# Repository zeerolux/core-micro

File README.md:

# Zeerolux Core-Micro

A lighting controller, control surface with 5 faders and 2 encoders, a USB DMX interface, an ARTNET node, and a standalone DMX generator. The Core-Micro system consists or 4 modules; the logic processor, the control surface, the DMX interface, and the redundant USB-C power supply. These modules are designed in a way that allows them to be iterated on separetly and allow for a limitless amount of configuration. How do you use Core-Micro? It depends on how YOU need to use it. Core-Micro can be used as a midi controller for On-PC lighting softwares, it can be used in a standalone mode where it acts like an all in one system for controlling stage lighting, and eventually it will be able to run in conjuction with other Zeerolux hardware and software as either the main controller or as a programming wing. It can also be used as an ARTNET node, this means that you can connect to it over the network and output DMX out its outputs.

### Defintions:
- DMX: Digital Multiplex is an RS485 based communication standard for controlling stage lights and equipment.
- ARTNET: DMX over IP
- On-PC: A standard term used by lighting consoles to describe control systems that require a laptop or PC to operate as opposed to all processing running on console.

### Why?
I decided to take on this project after I realised how incredibly expensive lighting consoles are. Out of curiosity, I wanted to see whether I could build my own console and what price it would turn out at. Another inspiration was my experience with the Avolites Quartz which to say the least was... frustrating, so naturally, I was fresh with ideas on what not to do.

## The Hardware
Core-Micro has four PCBs; one for each module. 

### Logic PCB:

The Logic PCB does a few main things:
- Connects to PC over USB
- Processes DMX signals and distrobutes them to DMX PCB(s)
- Runs ARTNET
- Interfaces with Surface PCB
All the main processing is powered by an RP2040 and the ethernet controller is a W5500.

### Control Surface PCB

This PCB's purpose is as follows:
- To have enough buttons to comfortably program lights
- To have enough faders for basic theatre applications
- To interface with the Logic board and passthrough control to PC applications or standalone mode.
Like the Logic PCB, the Control Surface is powered by an RP2040 and sends commands to other components via UART.

### Power PCB

Why do we need a separate PCB for power? Redundancy. In a live production environment, we cannot tolerate any power cuts or flaky USB connections. Therefore, I designed a board that has two inputs that can automatically be switched between if one cuts out. This allows for:
- Usage of independant power supplies for redundancy
- Automatic switch over to battery power during power cuts or brownouts
There is also a Superviser IC on this PCB in case I want to add that functionality in the future to other modules.

### DMX Interface PCB

This simple PCB converts the PIO DMX signal into RS485 signal that can be sent to DMX fixtures. This board also has both 3-pin and 5-pin XLR to ensure you can connect to any light.

## The Software

At this current moment, the software is a minimal version designed for testing DMX and ARTNET in a standalone mode. Here is the ideal list of software features I would like to implement:
- Standalone mode
- ARTNET node mode
- Midi Mode
- Custom serial driver for control via custom software

## BOM

## Bill of Materials (BOM)

| Item                          | Qty | Link / Supplier | List Price  | Actual  | Location    | Shipping  |
|--------------------------------|-----|-----------------|------------------|--------------|------------|----------------|
| Surface PCB                    | 5   | JLCPCB          | 17.90            | 190.94       | JLCPCB     | 33.14          |
| Surface PCB Assembly           | 2   | JLCPCB          | 39.89            | —            | aliexpress | —              |
| Logic PCB                      | 5   | JLCPCB          | 4.00             | —            | mouser     | 20.00          |
| Logic PCB Assembly             | 2   | JLCPCB          | 48.14            | —            | beekeeb    | 15.64          |
| DMX PCB                        | 5   | JLCPCB          | 4.00             | —            | —          | —              |
| DMX PCB Assembly               | 2   | JLCPCB          | 18.58            | —            | —          | —              |
| Power PCB                      | 5   | JLCPCB          | 2.00             | —            | —          | —              |
| Power PCB Assembly             | 2   | JLCPCB          | 43.29            | —            | —          | —              |
| Encoders                       | 3   | Mouser          | 5.07             | 5.07         | —          | —              |
| Faders                         | 5   | Mouser          | 9.60             | 9.60         | —          | —              |
| USB B Socket                   | 1   | Mouser          | 0.95             | 0.95         | —          | —              |
| Threaded Inserts M3            | 100 | AliExpress      | 5.00             | 5.00         | —          | —              |
| Threaded Inserts M2            | 100 | AliExpress      | 5.00             | 5.00         | —          | —              |
| Screws M3                      | 50  | AliExpress      | 3.00             | 3.00         | —          | —              |
| Screws M2                      | 50  | AliExpress      | 3.00             | 3.00         | —          | —              |
| Key Switches                   | 50  | Beekeeb         | 49.00            | 49.00        | —          | —              |
| Neutrik 3 Pin XLR              | 2   | Mouser          | 5.64             | 5.64         | —          | —              |
| Neutrik 5 Pin XLR              | 2   | Mouser          | 7.74             | 7.74         | —          | —              |
| Shipping (overall products)    | —   | —               | 68.78            | —            | —          | —              |
| **Total Cost**                 | —   | —               | **284.94**       | —            | —          | —              |

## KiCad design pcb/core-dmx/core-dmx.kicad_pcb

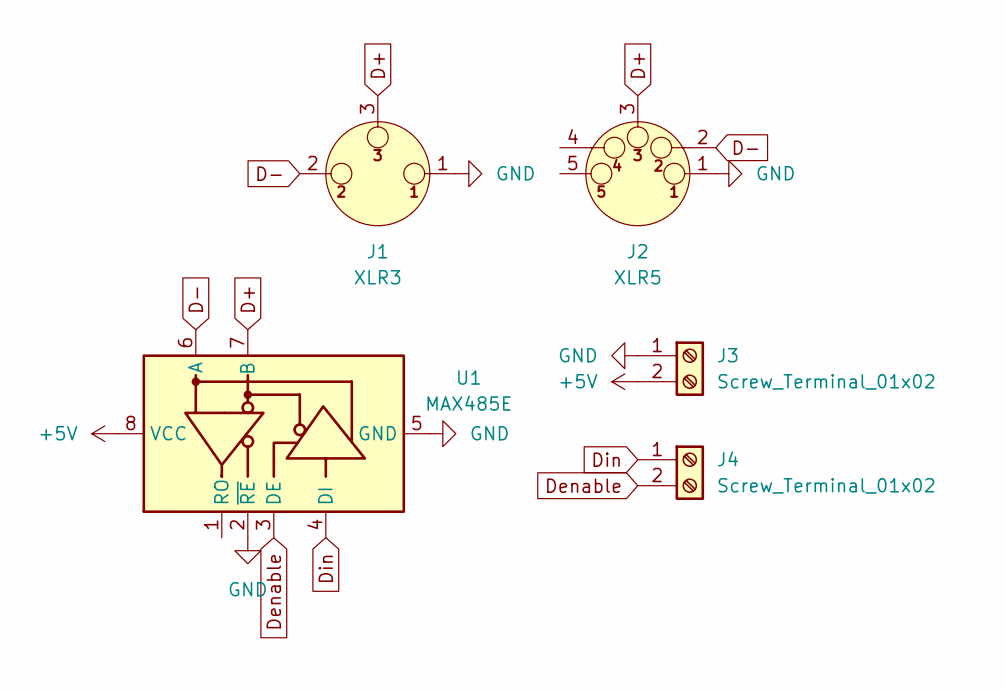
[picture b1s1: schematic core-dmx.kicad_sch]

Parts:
J1: XLR3; Jack_XLR_Neutrik_NC3FAH-0_Horizontal
J2: XLR5; Jack_XLR_Neutrik_NC5FAH-0_Horizontal
J3, J4: Screw_Terminal_01x02; TerminalBlock_Xinya_XY308-2.54-2P_1x02_P2.54mm_Horizontal
U1: MAX485E; SOIC-8_3.9x4.9mm_P1.27mm

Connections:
+5V: J3.2, U1.8 (VCC)
D+: J1.3, J2.3, U1.7 (B)
D-: J1.2, J2.2, U1.6 (A)
Denable: J4.2, U1.3 (DE)
Din: J4.1, U1.4 (DI)
GND: J1.1, J2.1, J3.1, U1.2 (~RE), U1.5 (GND)

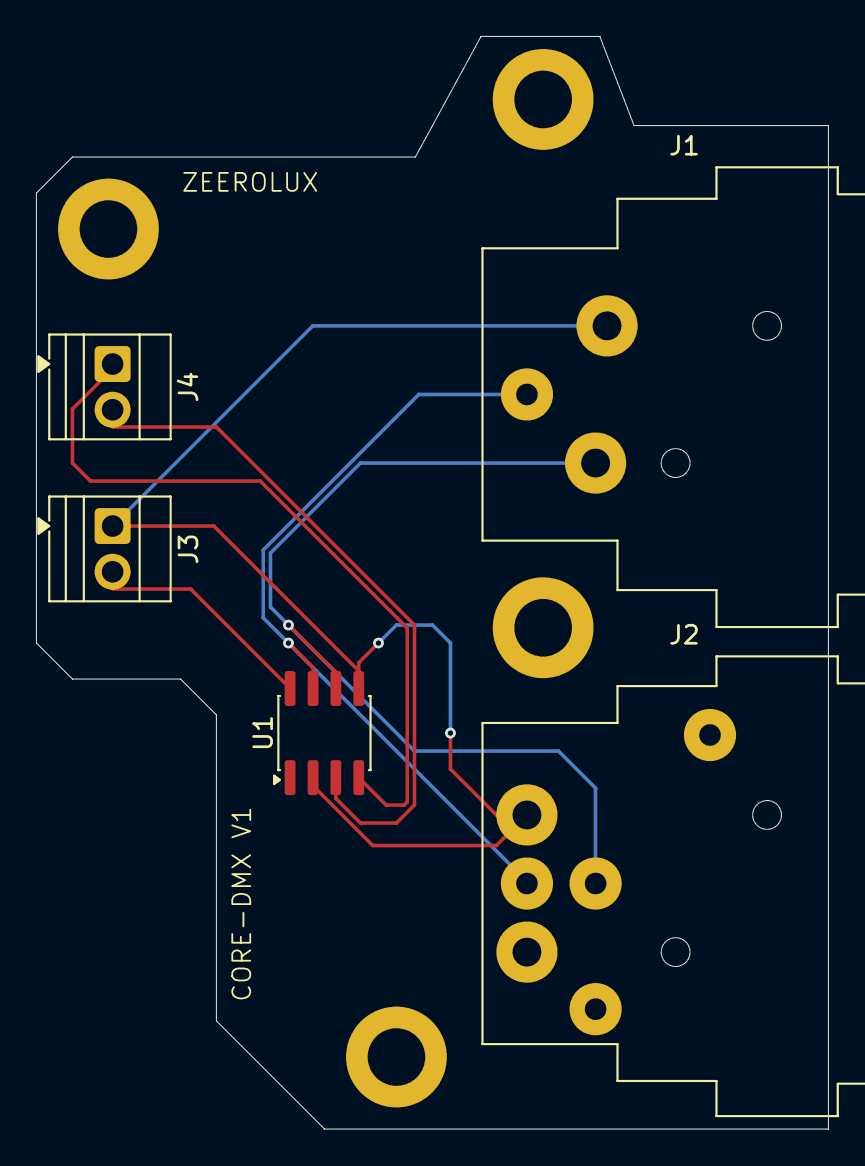
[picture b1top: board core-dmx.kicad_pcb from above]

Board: 2 copper layers, 44.0 x 60.7 mm, 5 parts (0 on the bottom side), 6 nets.

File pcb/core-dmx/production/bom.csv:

Designator,Footprint,Quantity,Value,LCSC Part #
"_3, _2, ",,3,,
"J3, J4",TerminalBlock_Xinya_XY308-2.54-2P_1x02_P2.54mm_Horizontal,2,Screw_Terminal_01x02,
U1,SOIC-8_3.9x4.9mm_P1.27mm,1,MAX485E,

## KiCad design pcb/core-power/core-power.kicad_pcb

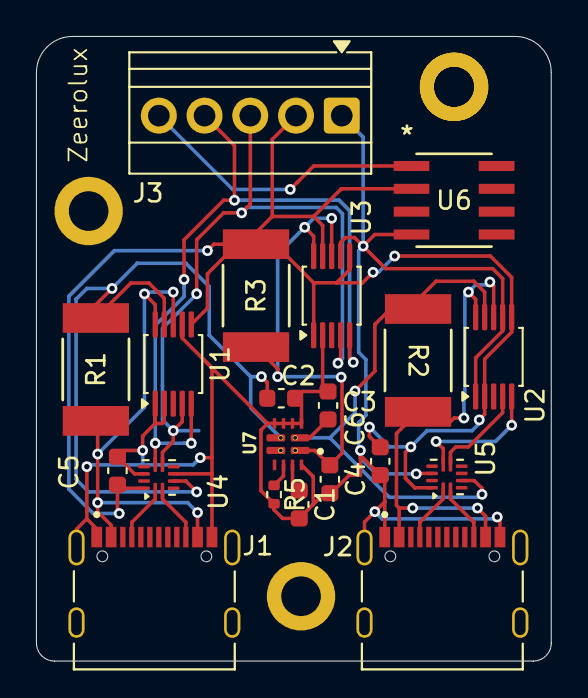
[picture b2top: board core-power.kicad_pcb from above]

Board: 2 copper layers, 28.6 x 34.7 mm, 20 parts (0 on the bottom side), 16 nets.

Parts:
C1: 22nF; C_0603_1608Metric
C2, C3: 10uF; C_0603_1608Metric
C4: 22uF; C_0603_1608Metric
C5, C6: 100nF; C_0603_1608Metric
J1, J2: USB_C_Receptacle_USB2.0_16P; HRO_TYPE-C-31-M-12
J3: Screw_Terminal_01x05; TerminalBlock_Xinya_XY308-2.54-5P_1x05_P2.54mm_Horizontal
R1, R2, R3: WSLP2512R0100FEA; RES_VISHAY_WSLP2512_C_VIS
R5: 5.5k; R_0402_1005Metric
U1, U2, U3: INA226; VSSOP-10_3x3mm_P0.5mm
U4, U5: TUSB320; Texas_X2QFN-12_1.6x1.6mm_P0.4mm
U6: MCP130T-315I/SN; SOIC8-N_MC_MCH
U7: TPS2121RUXR; IC_TPS2121RUXR

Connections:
CC1-1: J1.A5 (CC1), U4.1 (CC1)
CC1-2: J2.A5 (CC1), U5.1 (CC1)
CC2-1: J1.B5 (CC2), U4.2 (CC2)
CC2-2: J2.B5 (CC2), U5.2 (CC2)
GND: C1.2, C2.2, C3.2, C4.2, C5.2, C6.2, J1.GND, J1.S1 (SHIELD), J2.A1_B12, J2.B1_A12, J2.S1 (SHIELD), J3.1, R5.2, U1.1 (A1), U1.2 (A0), U1.7 (GND), U2.1 (A1), U2.7 (GND), U3.2 (A0), U3.7 (GND), U4.5 (ADDR), U4.10 (GND), U5.10 (GND), U6.4 (VSS), U7.3 (CP2), U7.4 (OV2), U7.5 (OV1), U7.6 (PR1), U7.12 (GND)
J1V+: J1.A4_B9, R1.1, U1.8 (Vbus), U1.10 (Vin+)
J1V-: C2.1, R1.2, U1.9 (Vin-), U4.4 (VBUS_DET), U7.7 (IN1), U7.7_1 (IN1__1)
J2V+: R2.2, U2.8 (Vbus), U2.10 (Vin+)
J2V-: C3.1, R2.1, U2.9 (Vin-), U5.4 (VBUS_DET), U7.2 (IN2), U7.2_1 (IN2__1)
MUXV+: C4.1, R3.1, U3.8 (Vbus), U3.10 (Vin+), U7.1 (OUT), U7.1_1 (OUT__1), U7.8 (OUT__2), U7.8_1 (OUT__3)
MUXV-: C5.1, C6.1, J3.2, R3.2, U1.6 (VS), U2.2 (A0), U2.6 (VS), U3.1 (A1), U3.6 (VS), U3.9 (Vin-), U4.12 (VDD), U5.5 (ADDR), U5.12 (VDD), U6.2 (VDD)
unnamed: R5.1, U7.10 (ILIM)
unnamed: C1.1, U7.11 (SS)
RESET: J3.5, U6.1 (*RST)
SCL: J3.4, U1.5 (SCL), U2.5 (SCL), U3.5 (SCL), U4.8 (SCL/OUT2), U5.8 (SCL/OUT2)
SDA: J3.3, U1.4 (SDA), U2.4 (SDA), U3.4 (SDA), U4.7 (SDA/OUT1), U5.7 (SDA/OUT1)

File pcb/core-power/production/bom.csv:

Designator,Footprint,Quantity,Value,LCSC Part #
,,1,,
C1,0603,1,22nF,
"C2, C3",0603,2,10uF,
C4,0603,1,22uF,
"C5, C6",0603,2,100nF,
"J1, J2",HRO_TYPE-C-31-M-12,2,USB_C_Receptacle_USB2.0_16P,
J3,TerminalBlock_Xinya_XY308-2.54-5P_1x05_P2.54mm_Horizontal,1,Screw_Terminal_01x05,
"R1, R2, R3",RES_VISHAY_WSLP2512_C_VIS,3,WSLP2512R0100FEA,
R5,0402,1,5.5k,
"U1, U2, U3",VSSOP-10_3x3mm_P0.5mm,3,INA226,
"U4, U5",Texas_X2QFN-12_1.6x1.6mm_P0.4mm,2,TUSB320,
U6,SOIC8-N_MC_MCH,1,MCP130T-315I/SN,
U7,IC_TPS2121RUXR,1,TPS2121RUXR,

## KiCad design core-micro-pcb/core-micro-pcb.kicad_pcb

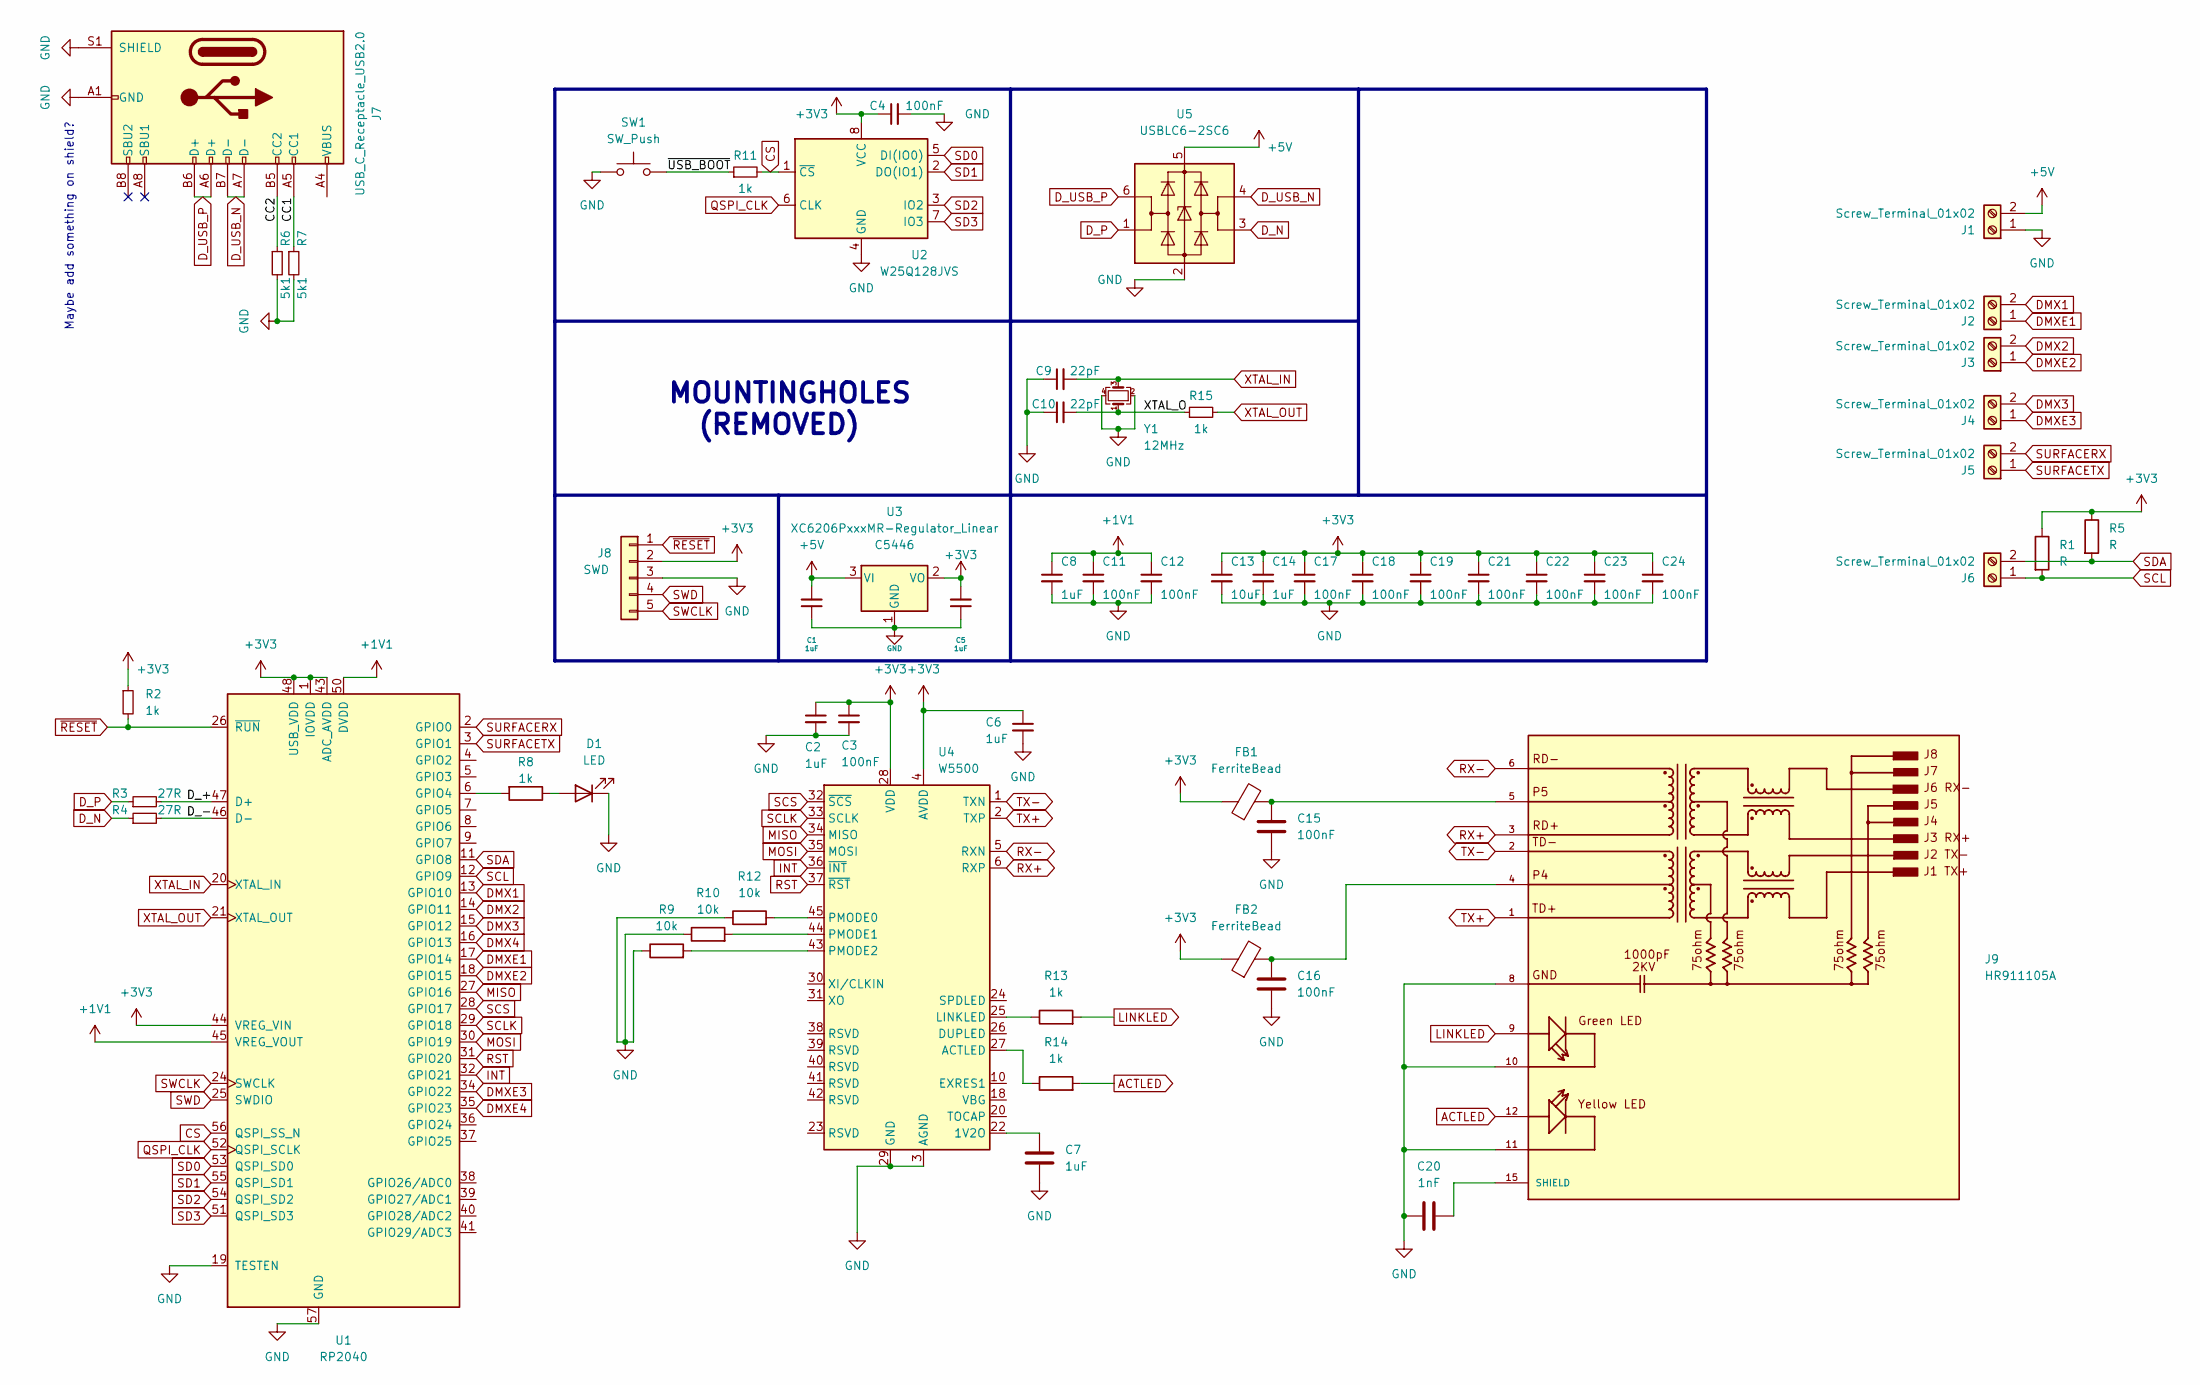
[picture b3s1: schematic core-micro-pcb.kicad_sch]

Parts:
C1, C5, C8, C14: 1uF; C_0402_1005Metric; LCSC C52923
C2, C6, C7: 1uF; C_0402_1005Metric
C3, C15, C16: 100nF; C_0402_1005Metric
C4, C11, C12, C17, C18, C19, C21, C22, C23, C24: 100nF; C_0402_1005Metric; LCSC C1525
C9, C10: 22pF; C_0402_1005Metric; LCSC C1555
C13: 10uF; C_0402_1005Metric; LCSC C15525
C20: 1nF; C_0402_1005Metric
D1: LED; LED_0201_0603Metric
FB1, FB2: FerriteBead; L_0603_1608Metric
J1, J2, J3, J4, J5, J6: Screw_Terminal_01x02; TerminalBlock_Xinya_XY308-2.54-2P_1x02_P2.54mm_Horizontal
J7: USB_C_Receptacle_USB2.0; HRO_TYPE-C-31-M-12; LCSC C165948
J8: SWD; PinSocket_1x05_P2.54mm_Vertical
J9: HR911105A; HANRUN_HR911105A; PARTREV A
R1, R5: R; R_0402_1005Metric
R2, R11, R15: 1k; R_0402_1005Metric; LCSC C11702
R3, R4: 27R; R_0603_1608Metric; LCSC C25190
R6, R7: 5k1; R_0402_1005Metric; LCSC C25905
R8, R13, R14: 1k; R_0402_1005Metric
R9, R10, R12: 10k; R_0402_1005Metric
SW1: SW_Push; PinSocket_1x02_P2.54mm_Vertical
U1: RP2040; QFN-56-1EP_7x7mm_P0.4mm_EP3.2x3.2mm_ThermalVias; LCSC C2040
U2: W25Q128JVS; SOIC127P790X216-8N; LCSC C131025
U3: XC6206PxxxMR-Regulator_Linear; SOT-23; LCSC C5446
U4: W5500; LQFP-48_7x7mm_P0.5mm
U5: USBLC6-2SC6; SOT-23-6; LCSC C2827654
Y1: 12MHz; Crystal_SMD_3225-4Pin_3.2x2.5mm; LCSC C9002

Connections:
+1V1: C8.1, C11.1, C12.1, U1.23 (DVDD), U1.45 (VREG_VOUT), U1.50 (DVDD)
+3V3: C2.1, C3.1, C4.1, C5.2, C6.1, C13.1, C14.1, C17.1, C18.1, C19.1, C21.1, C22.1, C23.1, C24.1, FB1.1, FB2.1, J8.2, R1.1, R2.1, R5.1, U1.1 (IOVDD), U1.10 (IOVDD), U1.22 (IOVDD), U1.33 (IOVDD), U1.42 (IOVDD), U1.43 (ADC_AVDD), U1.44 (VREG_VIN), U1.48 (USB_VDD), U1.49 (IOVDD), U2.8 (VCC), U3.2 (VO), U4.4 (AVDD), U4.8 (AVDD), U4.11 (AVDD), U4.15 (AVDD), U4.17 (AVDD), U4.21 (AVDD), U4.28 (VDD)
+5V: C1.2, J1.2, U3.3 (VI), U5.5 (VBUS)
/CC1: J7.A5 (CC1), R7.1
/CC2: J7.B5 (CC2), R6.1
/D_+: R3.2, U1.47 (D+)
/D_-: R4.2, U1.46 (D-)
/XTAL_O: C10.2, R15.1, Y1.1
/~USB_BOOT: R11.1, SW1.2
ACTLED: J9.12, R14.2
CS: R11.2, U1.56 (QSPI_SS_N), U2.1 (~CS)
DMX1: J2.2, U1.13 (GPIO10)
DMX2: J3.2, U1.14 (GPIO11)
DMX3: J4.2, U1.15 (GPIO12)
DMX4: U1.16 (GPIO13)
DMXE1: J2.1, U1.17 (GPIO14)
DMXE2: J3.1, U1.18 (GPIO15)
DMXE3: J4.1, U1.34 (GPIO22)
DMXE4: U1.35 (GPIO23)
D_N: R4.1, U5.3 (I/O2)
D_P: R3.1, U5.1 (I/O1)
D_USB_N: J7.A7 (D-), J7.B7 (D-), U5.4 (I/O2)
D_USB_P: J7.A6 (D+), J7.B6 (D+), U5.6 (I/O1)
GND: C1.1, C2.2, C3.2, C4.2, C5.1, C6.2, C7.2, C8.2, C9.1, C10.1, C11.2, C12.2, C13.2, C14.2, C15.2, C16.2, C17.2, C18.2, C19.2, C20.2, C21.2, C22.2, C23.2, C24.2, D1.1 (K), J1.1, J7.A1 (GND), J7.A12 (GND), J7.B1 (GND), J7.B12 (GND), J7.S1 (SHIELD), J8.3, J9.8, J9.10, J9.11, R6.2, R7.2, R9.1, R10.1, R12.1, SW1.1, U1.19 (TESTEN), U1.57 (GND), U2.4 (GND), U3.1 (GND), U4.3 (AGND), U4.9 (AGND), U4.14 (AGND), U4.16 (AGND), U4.19 (AGND), U4.29 (GND), U4.48 (AGND), U5.2 (GND), Y1.2, Y1.4
INT: U1.32 (GPIO21), U4.36 (~INT)
LINKLED: J9.9, R13.2
MISO: U1.27 (GPIO16), U4.34 (MISO)
MOSI: U1.30 (GPIO19), U4.35 (MOSI)
unnamed: C15.1, FB1.2, J9.5
unnamed: C16.1, FB2.2, J9.4
unnamed: C20.1, J9.15 (SHIELD), J9.16 (SHIELD)
unnamed: D1.2 (A), R8.1
unnamed: J7.A4 (VBUS), J7.A9 (VBUS), J7.B4 (VBUS), J7.B9 (VBUS)
unnamed: R8.2, U1.6 (GPIO4)
unnamed: C7.1, U4.22 (1V2O)
unnamed: R14.1, U4.27 (ACTLED)
unnamed: R13.1, U4.25 (LINKLED)
unnamed: R12.2, U4.45 (PMODE0)
unnamed: R10.2, U4.44 (PMODE1)
unnamed: R9.2, U4.43 (PMODE2)
QSPI_CLK: U1.52 (QSPI_SCLK), U2.6 (CLK)
RST: U1.31 (GPIO20), U4.37 (~RST)
RX+: J9.3, U4.6 (RXP)
RX-: J9.6, U4.5 (RXN)
SCL: J6.1, R1.2, U1.12 (GPIO9)
SCLK: U1.29 (GPIO18), U4.33 (SCLK)
SCS: U1.28 (GPIO17), U4.32 (~SCS)
SD0: U1.53 (QSPI_SD0), U2.5 (DI(IO0))
SD1: U1.55 (QSPI_SD1), U2.2 (DO(IO1))
SD2: U1.54 (QSPI_SD2), U2.3 (IO2)
SD3: U1.51 (QSPI_SD3), U2.7 (IO3)
SDA: J6.2, R5.2, U1.11 (GPIO8)
SURFACERX: J5.2, U1.2 (GPIO0)
SURFACETX: J5.1, U1.3 (GPIO1)
SWCLK: J8.5, U1.24 (SWCLK)
SWD: J8.4, U1.25 (SWDIO)
TX+: J9.1, U4.2 (TXP)
TX-: J9.2, U4.1 (TXN)
XTAL_IN: C9.2, U1.20 (XTAL_IN), Y1.3
XTAL_OUT: R15.2, U1.21 (XTAL_OUT)
~RESET: J8.1, R2.2, U1.26 (~RUN)

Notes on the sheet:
MOUNTINGHOLES (REMOVED)
Maybe add something on shield?

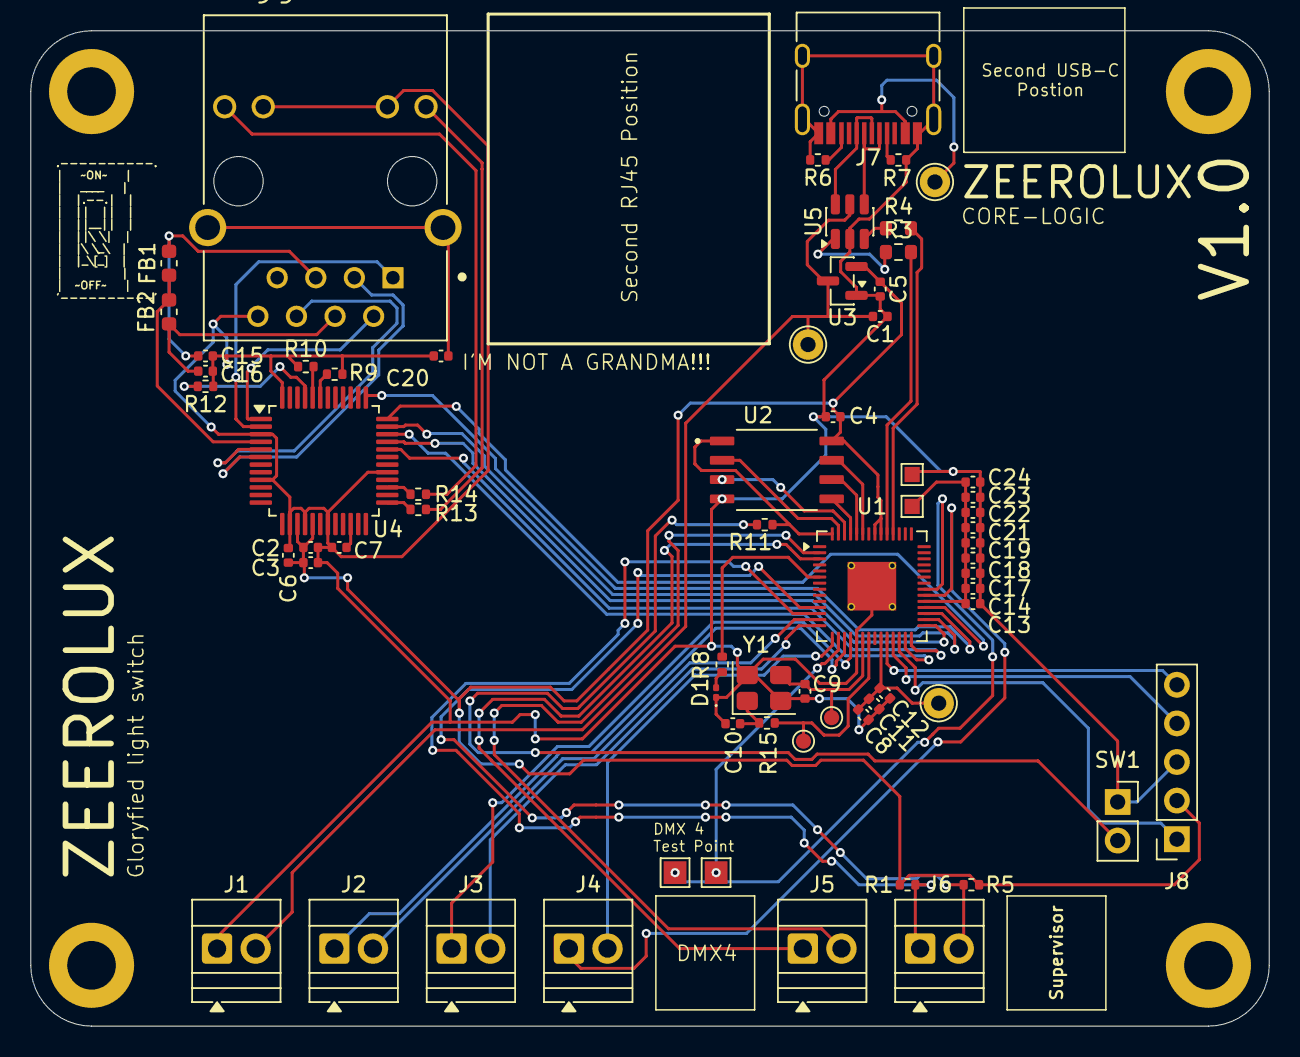
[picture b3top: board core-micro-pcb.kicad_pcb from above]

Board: 2 copper layers, 81.5 x 65.5 mm, 57 parts (0 on the bottom side), 59 nets.

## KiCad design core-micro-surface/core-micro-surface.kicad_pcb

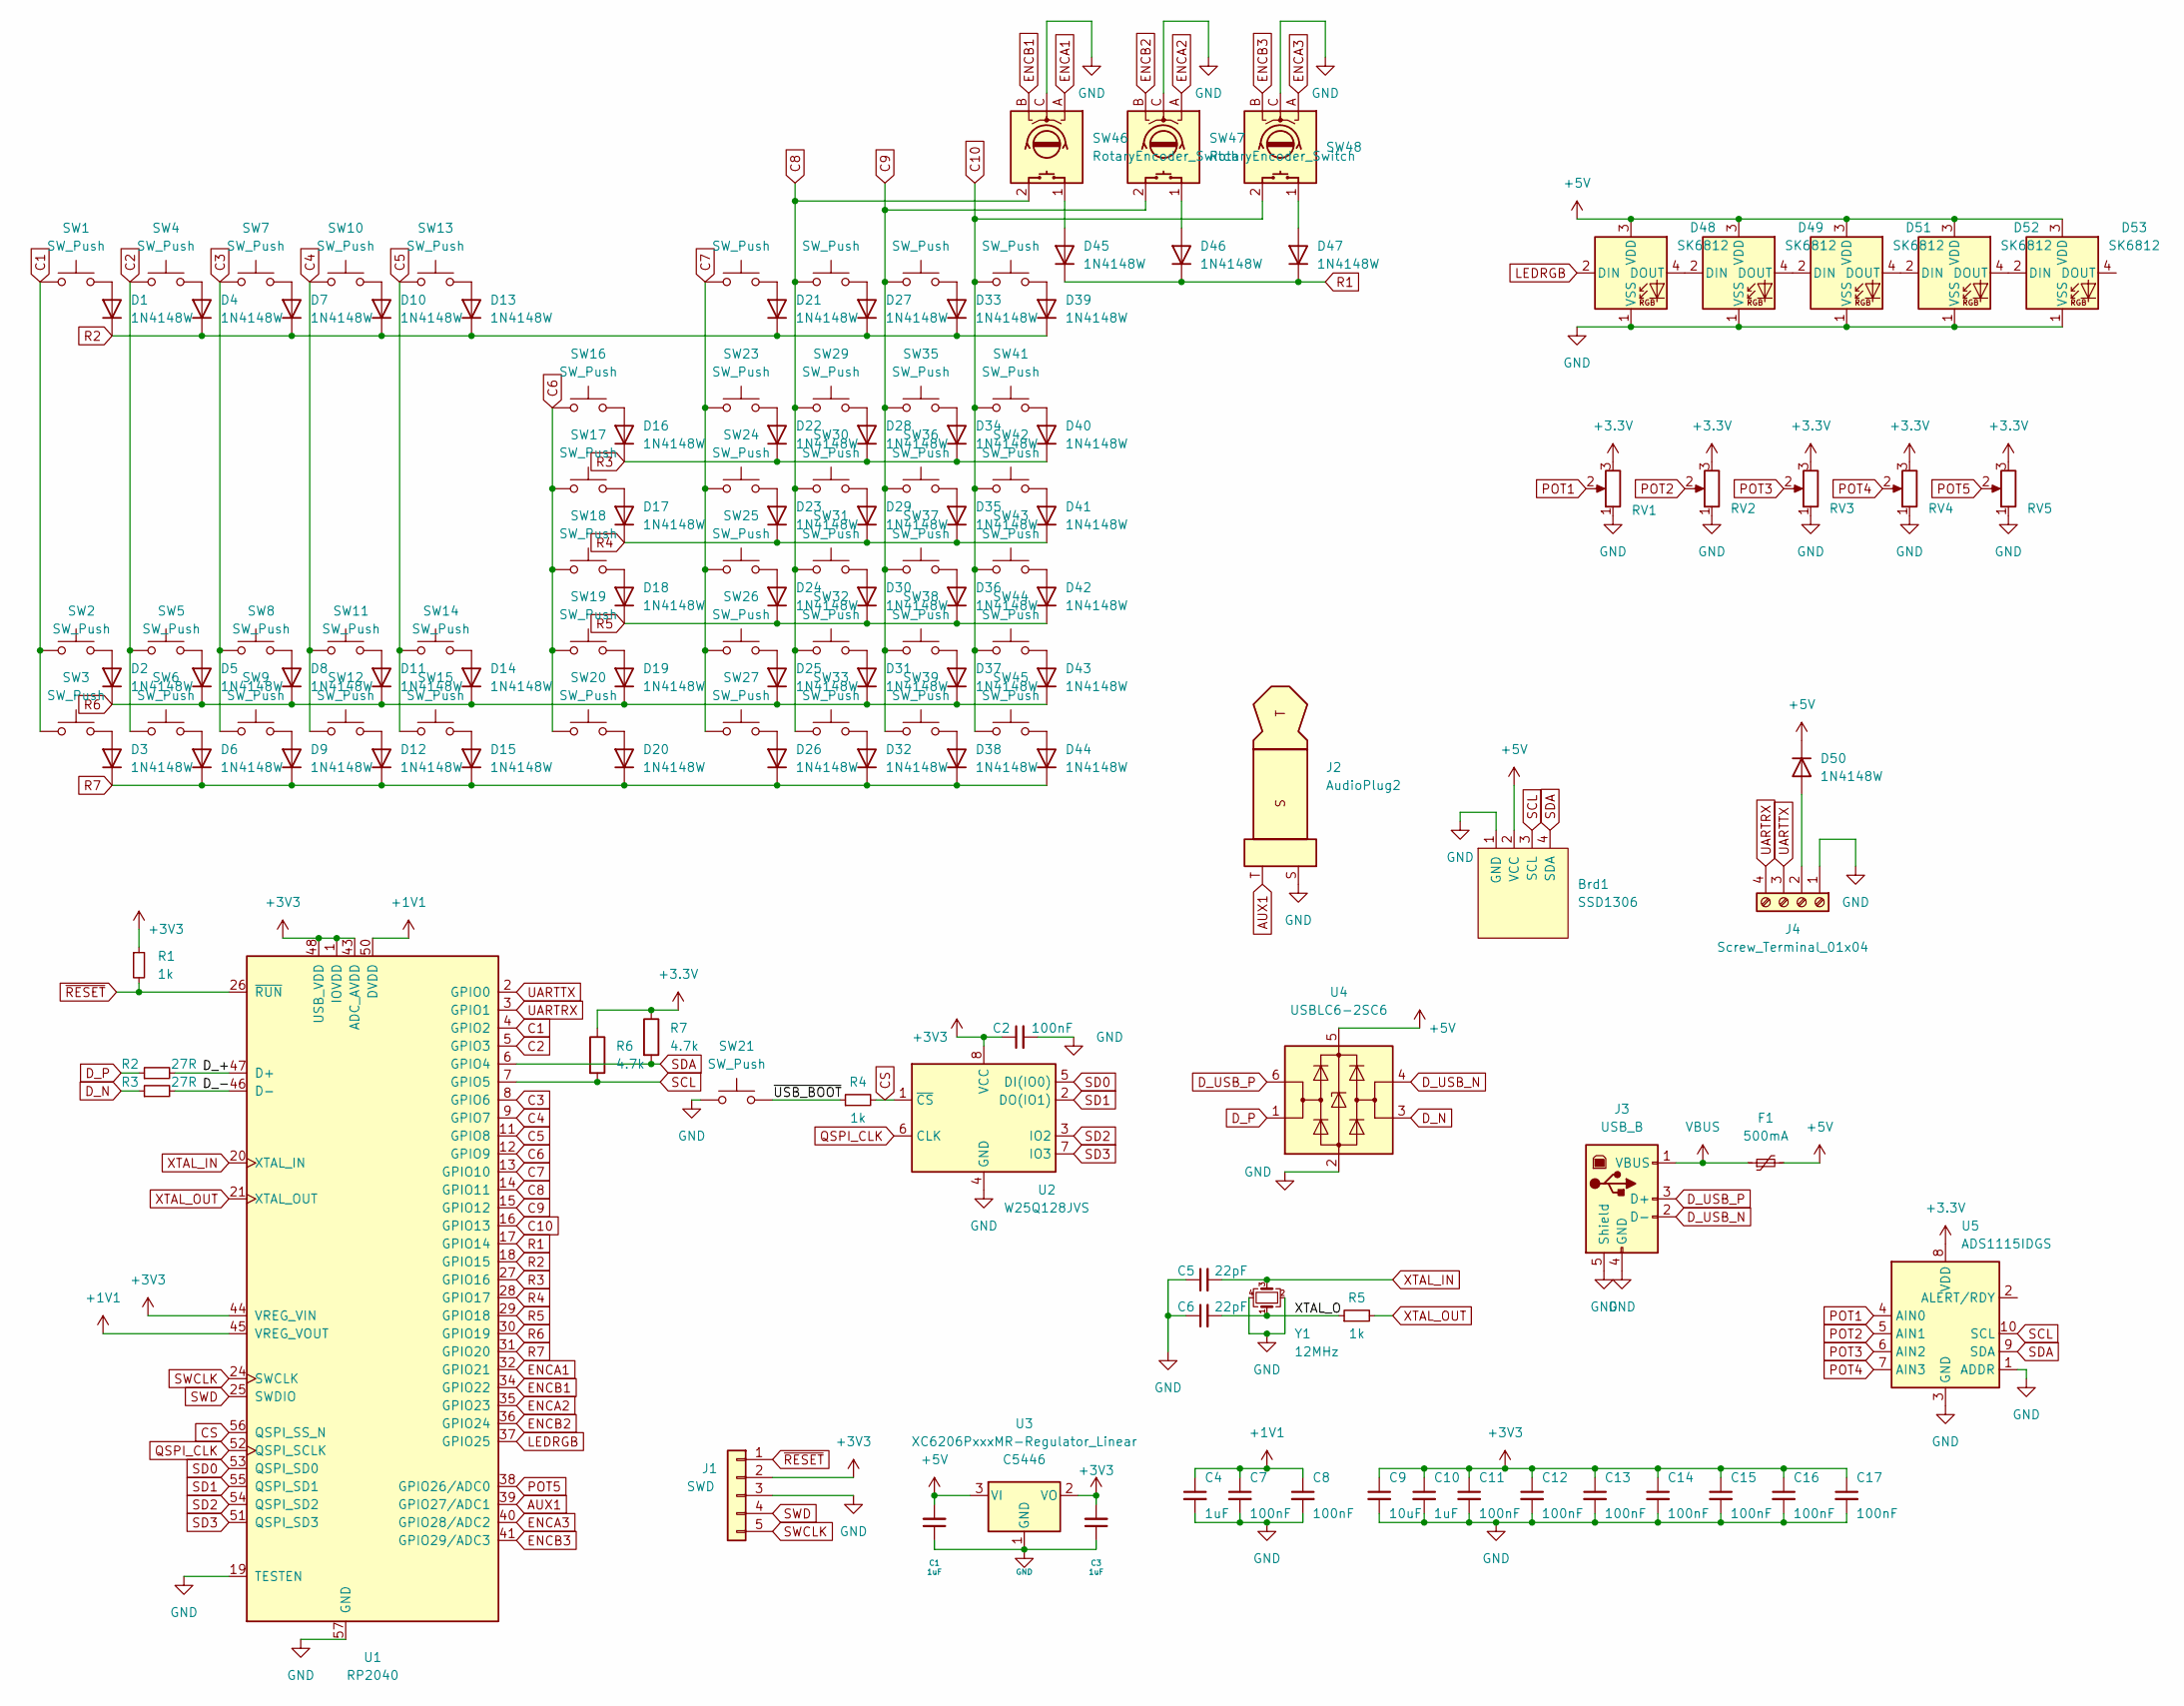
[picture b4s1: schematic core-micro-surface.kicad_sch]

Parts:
Brd1: SSD1306; 128x64OLED
C1, C3, C4, C10: 1uF; C_0402_1005Metric; LCSC C52923
C2, C7, C8, C11, C12, C13, C14, C15, C16, C17: 100nF; C_0402_1005Metric; LCSC C1525
C5, C6: 22pF; C_0402_1005Metric; LCSC C1555
C9: 10uF; C_0402_1005Metric; LCSC C15525
D1, D2, D3, D4, D5, D6, D7, D8, D9, D10, D11, D12, D13, D14, D15, D16, D17, D18, D19, D20, D21, D22, D23, D24, D25, D26, D27, D28, D29, D30, D31, D32, D33, D34, D35, D36, D37, D38, D39, D40, D41, D42, D43, D44, D45, D46, D47, D50: 1N4148W; D_SOD-123
D48, D49, D51, D52, D53: SK6812; LED_SK6812_PLCC4_5.0x5.0mm_P3.2mm
F1: 500mA; Fuse_1206_3216Metric; LCSC C70076
J1: SWD; PinSocket_1x05_P2.54mm_Vertical
J2: AudioPlug2; Jack_3.5mm_CUI_SJ-3523-SMT_Horizontal
J3: USB_B; USB_B_TE_5787834_Vertical
J4: Screw_Terminal_01x04; TerminalBlock_Xinya_XY308-2.54-4P_1x04_P2.54mm_Horizontal
R1, R4, R5: 1k; R_0402_1005Metric; LCSC C11702
R2, R3: 27R; R_0603_1608Metric; LCSC C25190
R6, R7: 4.7k; R_0402_1005Metric
RV1, RV2, RV3, RV4, RV5: R_Potentiometer; POT_PTA6043
SW1, SW2, SW3, SW4, SW5, SW6, SW7, SW8, SW9, SW10, SW11, SW12, SW13, SW14, SW15, SW16, SW17, SW18, SW19, SW20, SW22, SW23, SW24, SW25, SW26, SW27, SW28, SW29, SW30, SW31, SW32, SW33, SW34, SW35, SW36, SW37, SW38, SW39, SW40, SW41, SW42, SW43, SW44, SW45: SW_Push; SW_Hotswap_Kailh_Choc_V1V2_1.00u
SW21: SW_Push; PinSocket_1x02_P2.54mm_Vertical
SW46, SW47, SW48: RotaryEncoder_Switch; XDCR_PEC12R-4220F-S0024
U1: RP2040; QFN-56-1EP_7x7mm_P0.4mm_EP3.2x3.2mm; LCSC C2040
U2: W25Q128JVS; SOIC127P790X216-8N; LCSC C131025
U3: XC6206PxxxMR-Regulator_Linear; SOT-23; LCSC C5446
U4: USBLC6-2SC6; SOT-23-6; LCSC C2827654
U5: ADS1115IDGS; TSSOP-10_3x3mm_P0.5mm
Y1: 12MHz; Crystal_SMD_3225-4Pin_3.2x2.5mm; LCSC C9002

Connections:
+1V1: C4.1, C7.1, C8.1, U1.23 (DVDD), U1.45 (VREG_VOUT), U1.50 (DVDD)
+5V: Brd1.2 (VCC), C1.2, D48.3 (VDD), D49.3 (VDD), D50.1 (K), D51.3 (VDD), D52.3 (VDD), D53.3 (VDD), F1.2, U3.3 (VI), U4.5 (VBUS)
/D_+: R2.2, U1.47 (D+)
/D_-: R3.2, U1.46 (D-)
/XTAL_O: C6.2, R5.1, Y1.1
/~USB_BOOT: R4.1, SW21.2
AUX1: J2.T, U1.39 (GPIO27/ADC1)
C1: SW1.1, SW2.1, SW3.1, U1.4 (GPIO2)
C2: SW4.1, SW5.1, SW6.1, U1.5 (GPIO3)
C3: SW7.1, SW8.1, SW9.1, U1.8 (GPIO6)
C4: SW10.1, SW11.1, SW12.1, U1.9 (GPIO7)
C5: SW13.1, SW14.1, SW15.1, U1.11 (GPIO8)
C6: SW16.1, SW17.1, SW18.1, SW19.1, SW20.1, U1.12 (GPIO9)
C7: SW22.1, SW23.1, SW24.1, SW25.1, SW26.1, SW27.1, U1.13 (GPIO10)
C8: SW28.1, SW29.1, SW30.1, SW31.1, SW32.1, SW33.1, SW46.2 (S2), U1.14 (GPIO11)
C9: SW34.1, SW35.1, SW36.1, SW37.1, SW38.1, SW39.1, SW47.2 (2S2), U1.15 (GPIO12)
C10: SW40.1, SW41.1, SW42.1, SW43.1, SW44.1, SW45.1, SW48.2 (S2), U1.16 (GPIO13)
CS: R4.2, U1.56 (QSPI_SS_N), U2.1 (~CS)
D_N: R3.1, U4.3 (I/O2)
D_P: R2.1, U4.1 (I/O1)
D_USB_N: J3.2 (D-), U4.4 (I/O2)
D_USB_P: J3.3 (D+), U4.6 (I/O1)
ENCA1: SW46.A, U1.32 (GPIO21)
ENCA2: SW47.A, U1.35 (GPIO23)
ENCA3: SW48.A, U1.40 (GPIO28/ADC2)
ENCB1: SW46.B, U1.34 (GPIO22)
ENCB2: SW47.B, U1.36 (GPIO24)
ENCB3: SW48.B, U1.41 (GPIO29/ADC3)
GND: Brd1.1 (GND), C1.1, C2.2, C3.1, C4.2, C5.1, C6.1, C7.2, C8.2, C9.2, C10.2, C11.2, C12.2, C13.2, C14.2, C15.2, C16.2, C17.2, D48.1 (VSS), D49.1 (VSS), D51.1 (VSS), D52.1 (VSS), D53.1 (VSS), J1.3, J2.S, J3.4 (GND), J3.5 (Shield), J4.1, RV1.1, RV2.1, RV3.1, RV4.1, RV5.1, SW21.1, SW46.C, SW47.C, SW48.C, U1.19 (TESTEN), U1.57 (GND), U2.4 (GND), U3.1 (GND), U4.2 (GND), U5.1 (ADDR), U5.3 (GND), Y1.2, Y1.4
LEDRGB: D48.2 (DIN), U1.37 (GPIO25)
unnamed: D1.2 (A), SW1.2
unnamed: D2.2 (A), SW2.2
unnamed: D3.2 (A), SW3.2
unnamed: D4.2 (A), SW4.2
unnamed: D5.2 (A), SW5.2
unnamed: D6.2 (A), SW6.2
unnamed: D7.2 (A), SW7.2
unnamed: D8.2 (A), SW8.2
unnamed: D9.2 (A), SW9.2
unnamed: D10.2 (A), SW10.2
unnamed: D11.2 (A), SW11.2
unnamed: D12.2 (A), SW12.2
unnamed: D13.2 (A), SW13.2
unnamed: D14.2 (A), SW14.2
unnamed: D15.2 (A), SW15.2
unnamed: D16.2 (A), SW16.2
unnamed: D17.2 (A), SW17.2
unnamed: D18.2 (A), SW18.2
unnamed: D19.2 (A), SW19.2
unnamed: D20.2 (A), SW20.2
unnamed: D21.2 (A), SW22.2
unnamed: D22.2 (A), SW23.2
unnamed: D23.2 (A), SW24.2
unnamed: D24.2 (A), SW25.2
unnamed: D25.2 (A), SW26.2
unnamed: D26.2 (A), SW27.2
unnamed: D27.2 (A), SW28.2
unnamed: D28.2 (A), SW29.2
unnamed: D29.2 (A), SW30.2
unnamed: D30.2 (A), SW31.2
unnamed: D31.2 (A), SW32.2
unnamed: D32.2 (A), SW33.2
unnamed: D33.2 (A), SW34.2
unnamed: D34.2 (A), SW35.2
unnamed: D35.2 (A), SW36.2
unnamed: D36.2 (A), SW37.2
unnamed: D37.2 (A), SW38.2
unnamed: D38.2 (A), SW39.2
unnamed: D39.2 (A), SW40.2
unnamed: D40.2 (A), SW41.2
unnamed: D41.2 (A), SW42.2
unnamed: D42.2 (A), SW43.2
unnamed: D43.2 (A), SW44.2
unnamed: D44.2 (A), SW45.2
unnamed: D45.2 (A), SW46.1 (S1)
unnamed: D46.2 (A), SW47.1 (S1)
unnamed: D47.2 (A), SW48.1 (S1)
unnamed: D48.4 (DOUT), D49.2 (DIN)
unnamed: D49.4 (DOUT), D51.2 (DIN)
unnamed: D50.2 (A), J4.2
unnamed: D51.4 (DOUT), D52.2 (DIN)
unnamed: D52.4 (DOUT), D53.2 (DIN)
POT1: RV1.2, U5.4 (AIN0)
POT2: RV2.2, U5.5 (AIN1)
POT3: RV3.2, U5.6 (AIN2)
POT4: RV4.2, U5.7 (AIN3)
POT5: RV5.2, U1.38 (GPIO26/ADC0)
QSPI_CLK: U1.52 (QSPI_SCLK), U2.6 (CLK)
R1: D45.1 (K), D46.1 (K), D47.1 (K), U1.17 (GPIO14)
R2: D1.1 (K), D4.1 (K), D7.1 (K), D10.1 (K), D13.1 (K), D21.1 (K), D27.1 (K), D33.1 (K), D39.1 (K), U1.18 (GPIO15)
R3: D16.1 (K), D22.1 (K), D28.1 (K), D34.1 (K), D40.1 (K), U1.27 (GPIO16)
R4: D17.1 (K), D23.1 (K), D29.1 (K), D35.1 (K), D41.1 (K), U1.28 (GPIO17)
R5: D18.1 (K), D24.1 (K), D30.1 (K), D36.1 (K), D42.1 (K), U1.29 (GPIO18)
R6: D2.1 (K), D5.1 (K), D8.1 (K), D11.1 (K), D14.1 (K), D19.1 (K), D25.1 (K), D31.1 (K), D37.1 (K), D43.1 (K), U1.30 (GPIO19)
R7: D3.1 (K), D6.1 (K), D9.1 (K), D12.1 (K), D15.1 (K), D20.1 (K), D26.1 (K), D32.1 (K), D38.1 (K), D44.1 (K), U1.31 (GPIO20)
SCL: Brd1.3 (SCL), R6.2, U1.7 (GPIO5), U5.10 (SCL)
SD0: U1.53 (QSPI_SD0), U2.5 (DI(IO0))
SD1: U1.55 (QSPI_SD1), U2.2 (DO(IO1))
SD2: U1.54 (QSPI_SD2), U2.3 (IO2)
SD3: U1.51 (QSPI_SD3), U2.7 (IO3)
SDA: Brd1.4 (SDA), R7.2, U1.6 (GPIO4), U5.9 (SDA)
SWCLK: J1.5, U1.24 (SWCLK)
SWD: J1.4, U1.25 (SWDIO)
UARTRX: J4.4, U1.3 (GPIO1)
UARTTX: J4.3, U1.2 (GPIO0)
VBUS: F1.1, J3.1 (VBUS)
XTAL_IN: C5.2, U1.20 (XTAL_IN), Y1.3
XTAL_OUT: R5.2, U1.21 (XTAL_OUT)
~RESET: J1.1, R1.2, U1.26 (~RUN)

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
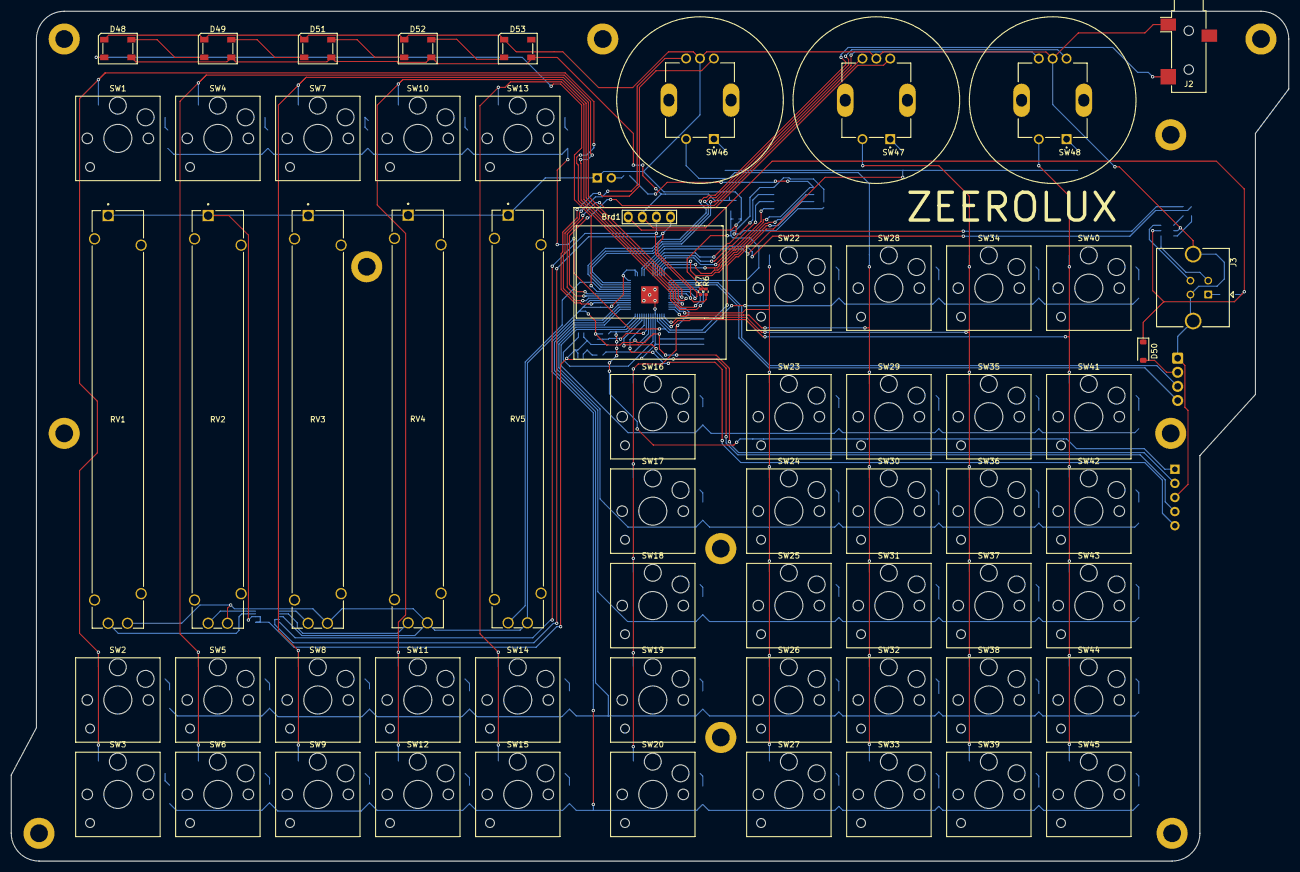
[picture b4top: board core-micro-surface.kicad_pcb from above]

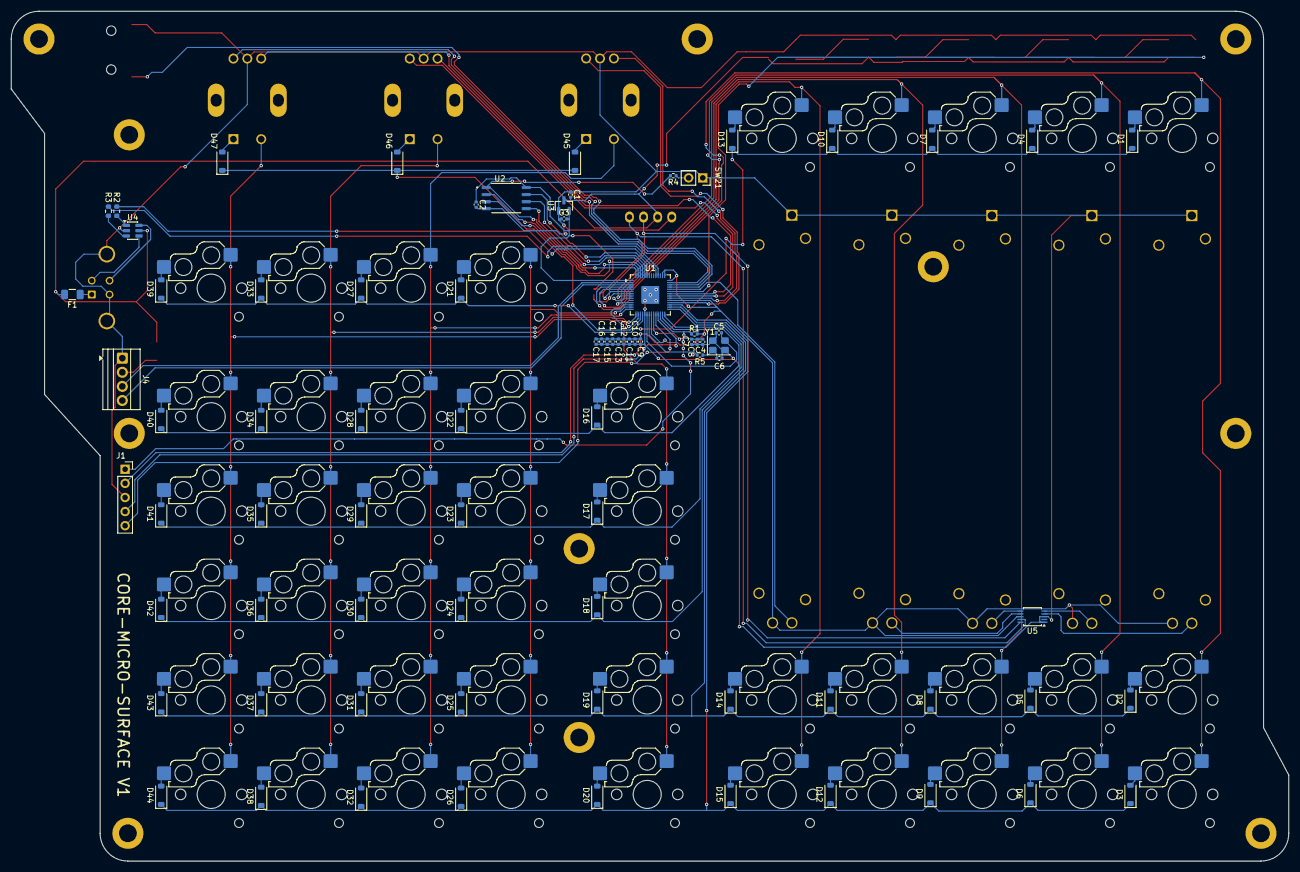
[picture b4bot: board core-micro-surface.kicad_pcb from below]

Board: 2 copper layers, 230.0 x 153.0 mm, 142 parts (79 on the bottom side), 111 nets.
